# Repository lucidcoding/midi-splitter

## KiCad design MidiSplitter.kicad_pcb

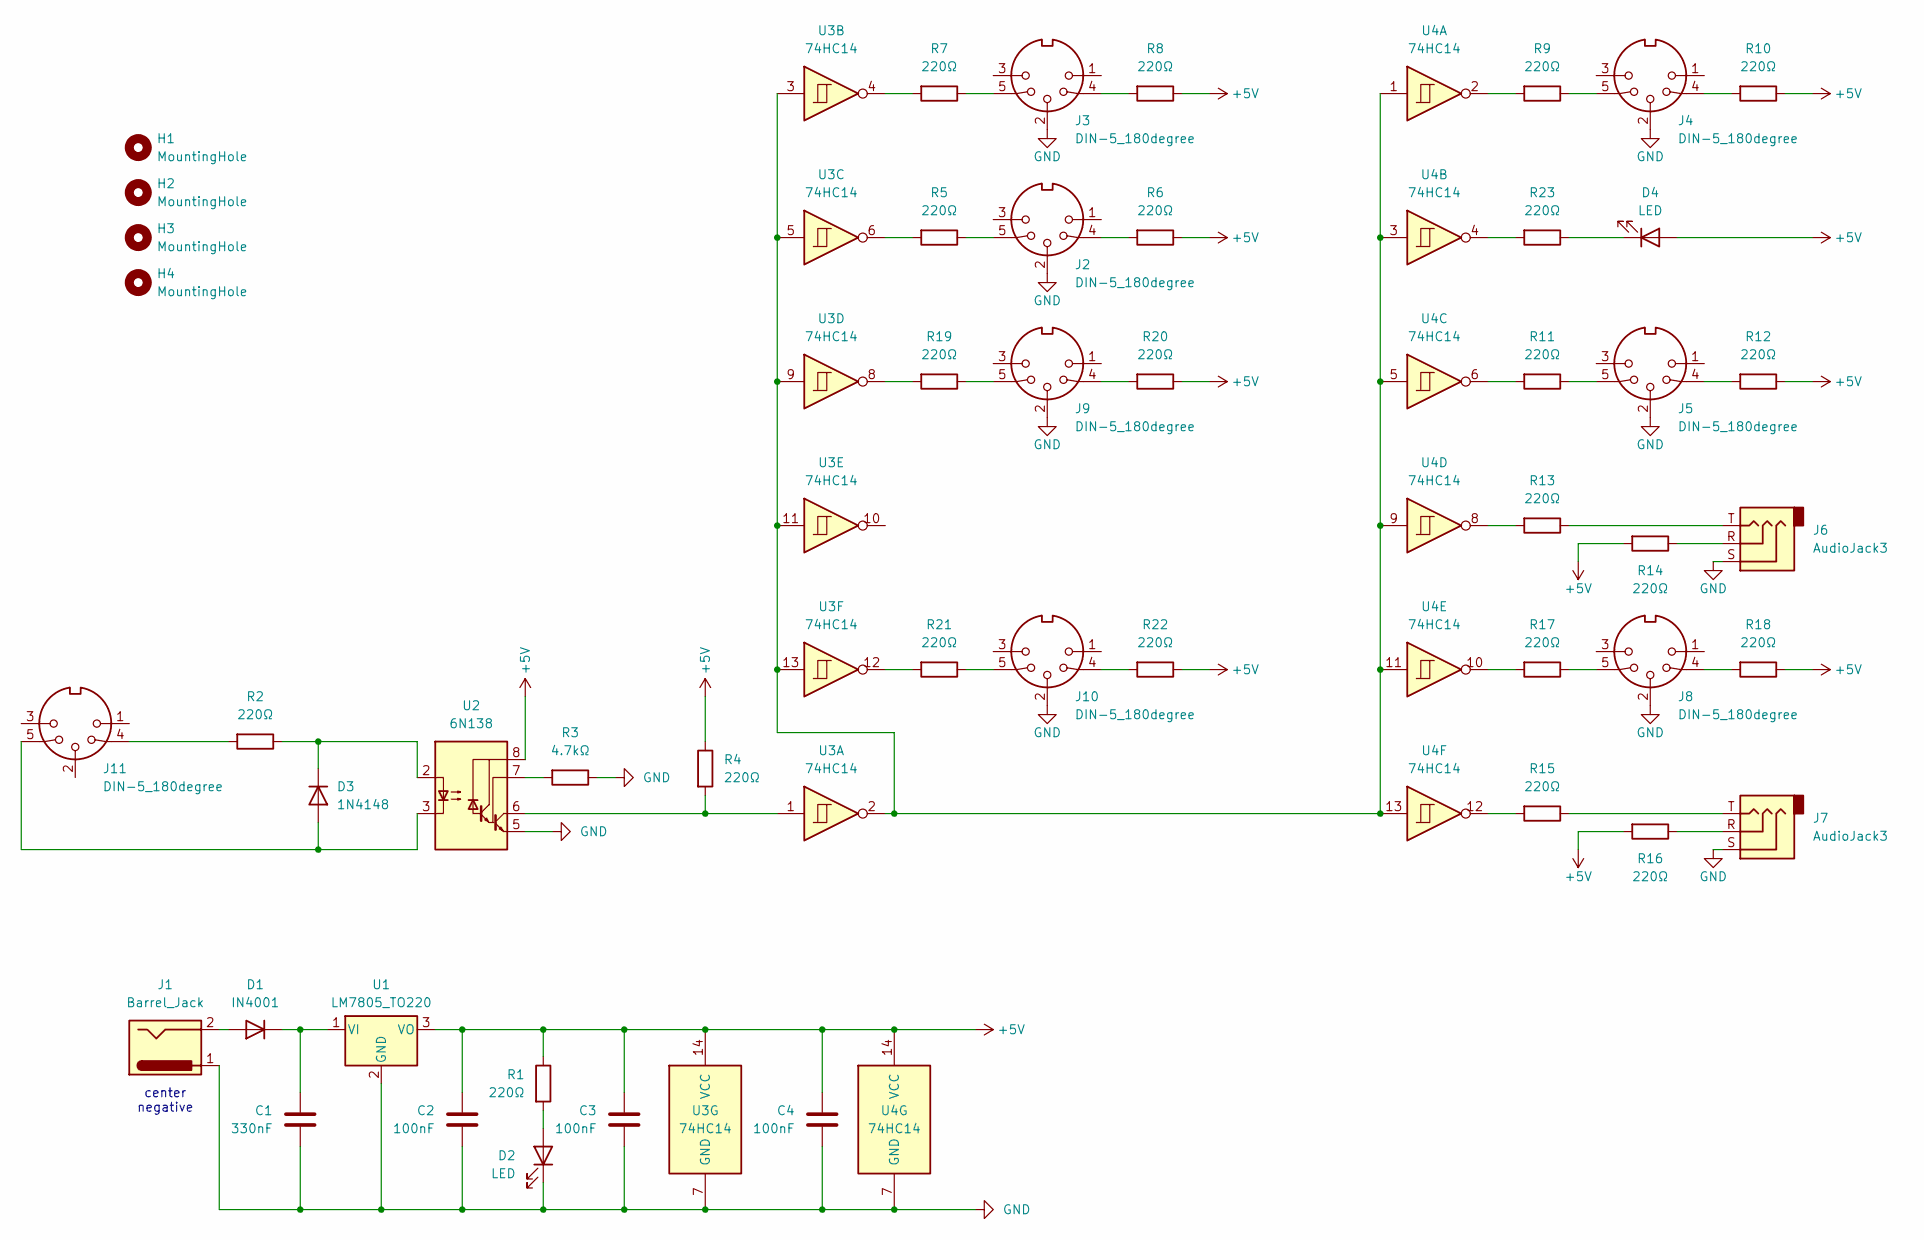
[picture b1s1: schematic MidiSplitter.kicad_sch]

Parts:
C1: 330nF; C_Disc_D5.0mm_W2.5mm_P5.00mm
C2, C3, C4: 100nF; C_Disc_D5.0mm_W2.5mm_P5.00mm
D1: IN4001; D_DO-35_SOD27_P7.62mm_Horizontal
D2, D4: LED; LED_D3.0mm
D3: 1N4148; D_DO-35_SOD27_P7.62mm_Horizontal
H1, H2, H3, H4: MountingHole; MountingHole_3.2mm_M3_DIN965_Pad
J1: Barrel_Jack; BarrelJack_GCT_DCJ200-10-A_Horizontal
J2, J3, J4, J5, J8, J9, J10, J11: DIN-5_180degree; MIDI_DIN5
J6, J7: AudioJack3; PJ-307
R1, R2, R4, R5, R6, R7, R8, R9, R10, R11, R12, R13, R14, R15, R16, R17, R18, R19, R20, R21, R22, R23: 220Ω; R_Axial_DIN0207_L6.3mm_D2.5mm_P7.62mm_Horizontal
R3: 4.7kΩ; R_Axial_DIN0207_L6.3mm_D2.5mm_P7.62mm_Horizontal
U1: LM7805_TO220; TO-220-3_Vertical
U2: 6N138; DIP-8_W7.62mm_Socket
U3, U4: 74HC14; DIP-14_W7.62mm_Socket

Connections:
+5V: C2.1, C3.1, C4.1, D4.2 (A), R1.1, R4.1, R6.1, R8.1, R10.1, R12.1, R14.2, R16.2, R18.1, R20.1, R22.1, U1.3 (VO), U2.8 (VCC), U3.14 (VCC), U4.14 (VCC)
GND: C1.2, C2.2, C3.2, C4.2, D2.1 (K), J1.1, J2.2, J3.2, J4.2, J5.2, J6.S, J7.S, J8.2, J9.2, J10.2, R3.1, U1.2 (GND), U2.5 (GND), U3.7 (GND), U4.7 (GND)
unnamed: D1.2 (A), J1.2
unnamed: C1.1, D1.1 (K), U1.1 (VI)
unnamed: D2.2 (A), R1.2
unnamed: D3.2 (A), J11.5, U2.3 (C2)
unnamed: D3.1 (K), R2.1, U2.2 (C1)
unnamed: D4.1 (K), R23.1
unnamed: J2.4, R6.2
unnamed: J2.5, R5.1
unnamed: J3.4, R8.2
unnamed: J3.5, R7.1
unnamed: J4.4, R10.2
unnamed: J4.5, R9.1
unnamed: J5.4, R12.2
unnamed: J5.5, R11.1
unnamed: J6.R, R14.1
unnamed: J6.T, R13.1
unnamed: J7.R, R16.1
unnamed: J7.T, R15.1
unnamed: J8.4, R18.2
unnamed: J8.5, R17.1
unnamed: J9.4, R20.2
unnamed: J9.5, R19.1
unnamed: J10.4, R22.2
unnamed: J10.5, R21.1
unnamed: J11.4, R2.2
unnamed: R5.2, U3.6
unnamed: R7.2, U3.4
unnamed: R9.2, U4.2
unnamed: R11.2, U4.6
unnamed: R13.2, U4.8
unnamed: R15.2, U4.12
unnamed: R17.2, U4.10
unnamed: R19.2, U3.8
unnamed: R21.2, U3.12
unnamed: R23.2, U4.4
unnamed: R3.2, U2.7 (VO1)
unnamed: R4.2, U2.6 (VO2), U3.1
unnamed: U3.2, U3.3, U3.5, U3.9, U3.11, U3.13, U4.1, U4.3, U4.5, U4.9, U4.11, U4.13

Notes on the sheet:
center negative

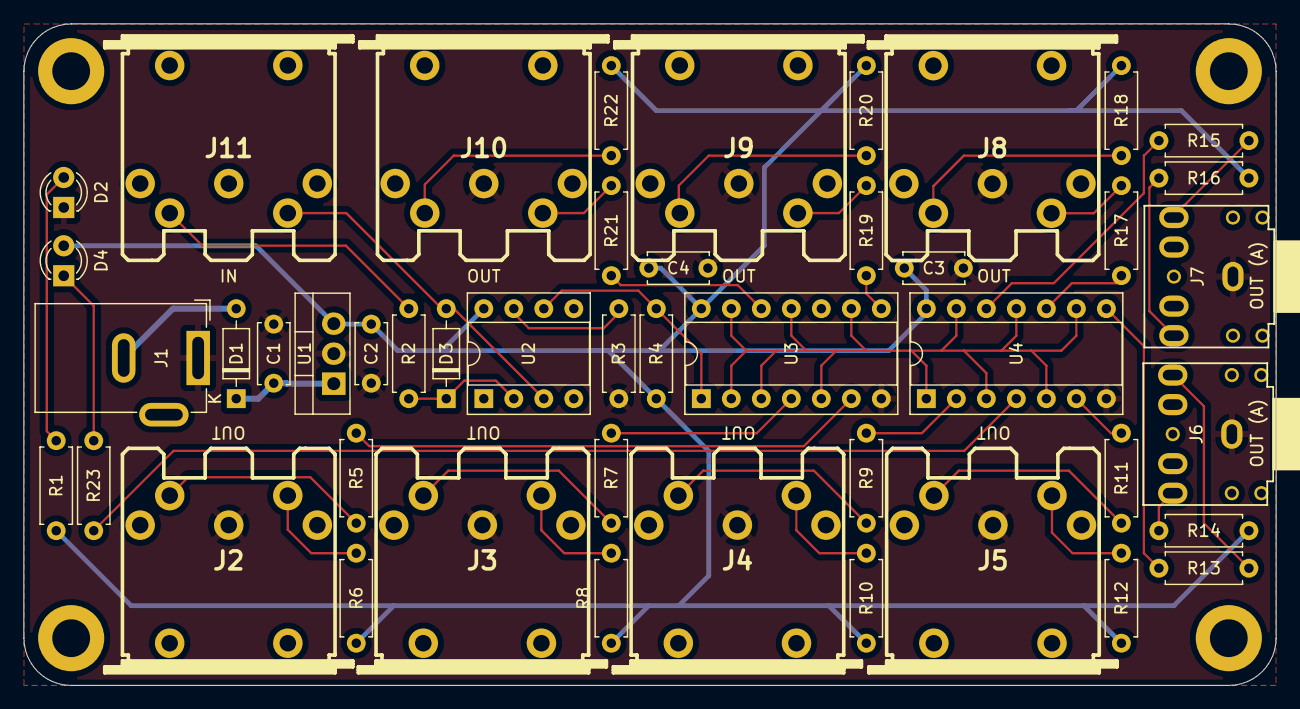
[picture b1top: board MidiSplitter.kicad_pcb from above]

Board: 2 copper layers, 106.0 x 56.0 mm, 50 parts (0 on the bottom side), 40 nets.

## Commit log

2025-06-16 Working version
